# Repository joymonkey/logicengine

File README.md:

# logicengine
Info, Hardware Files and Arduino Sketches for the RSeries Logic Engine.

Assembly instructions and documentation can be found in the GitHub wiki here...
https://github.com/joymonkey/logicengine/wiki

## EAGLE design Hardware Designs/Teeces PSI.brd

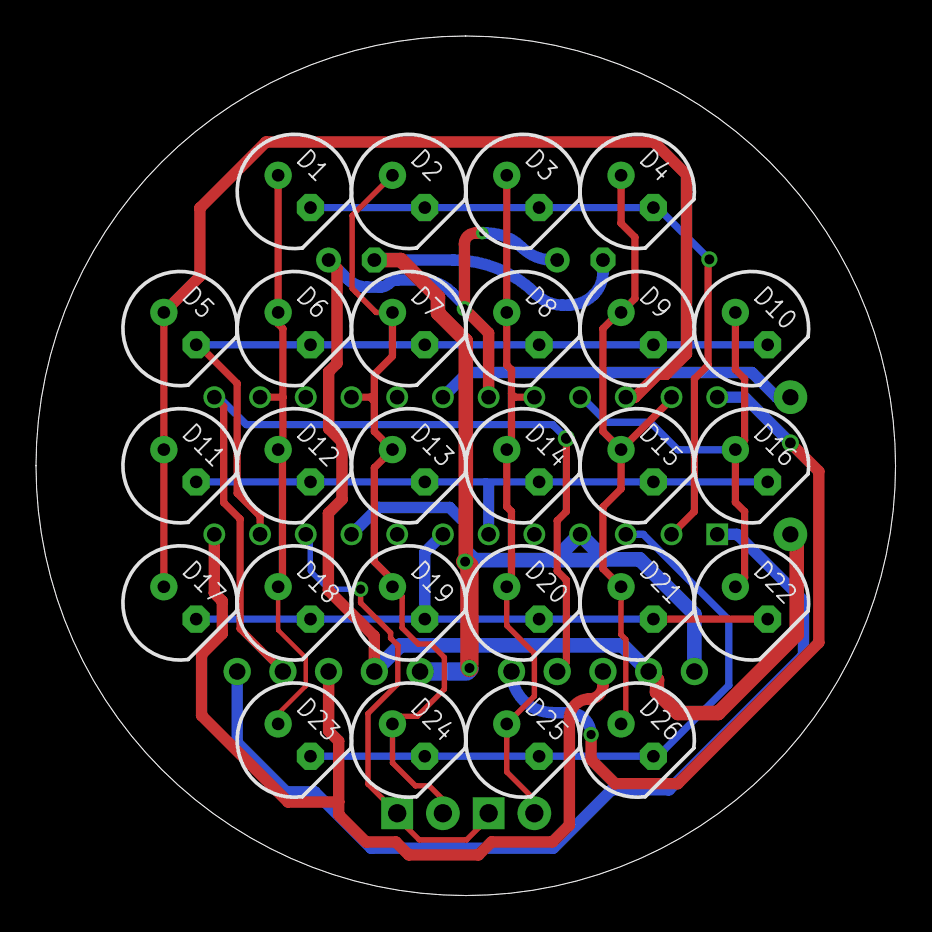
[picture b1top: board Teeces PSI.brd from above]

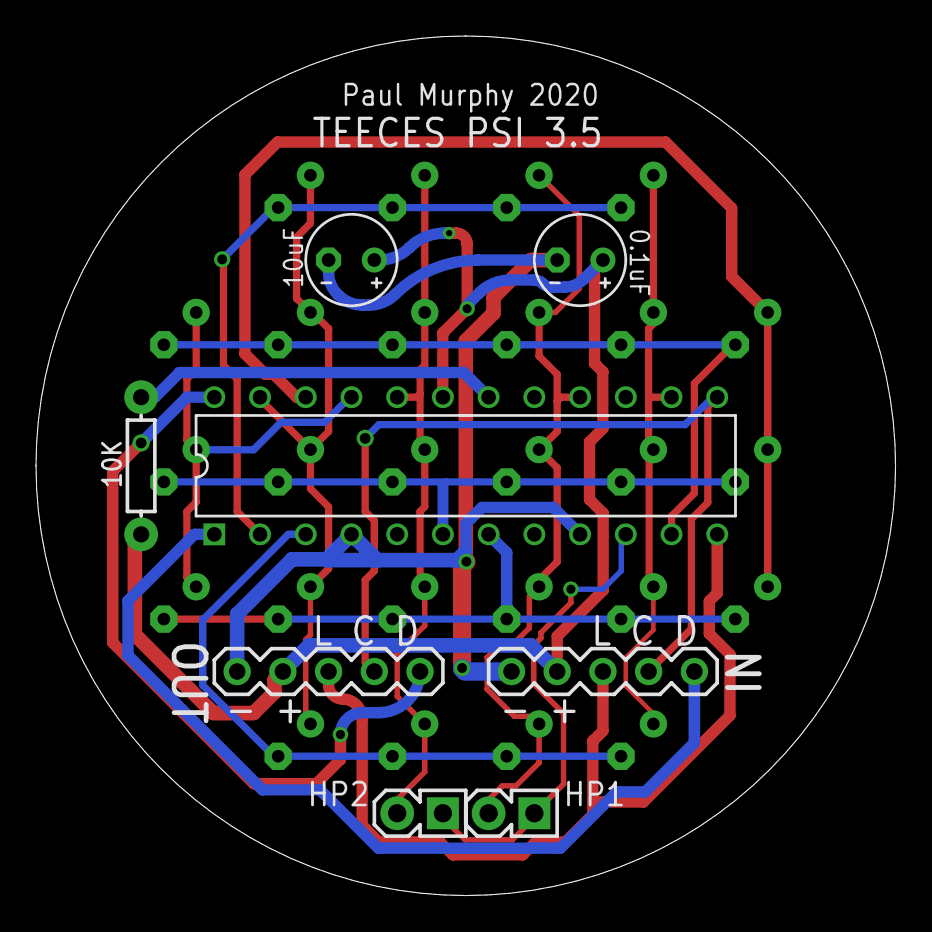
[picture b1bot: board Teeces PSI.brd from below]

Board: 2 copper layers, 47.8 x 47.8 mm, 34 parts (8 on the bottom side), 19 nets.

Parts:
C5: 10uF; E2,5-5
C6: 0.1uF; E2,5-5
D1, D2, D3, D4, D5, D6, D7, D8, D9, D10, D11, D12, D13, D14, D15, D16, D17, D18, D19, D20, D21, D22, D23, D24, D25, D26: LED5MM_SLIM
HP1, HP2: 1X02-SQ
IC2: MAX7219CNG; DIP24-3
IN: 1X05
OUT: 1X05
R2: 10K; AXIAL-0.3

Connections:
+5V: C5.+, C6.+, IC2.19, IN.2, OUT.2, R2.P$2
CLK: IC2.13, IN.4, OUT.4
DIG0: D1.K, D2.K, D3.K, D4.K, IC2.2
DIG1: D5.K, D6.K, D7.K, D8.K, D9.K, D10.K, IC2.11
DIG2: D11.K, D12.K, D13.K, D14.K, D15.K, D16.K, IC2.6
DIG3: D17.K, D18.K, D19.K, D20.K, D21.K, D22.K, IC2.7
DIG4: D23.K, D24.K, D25.K, D26.K, IC2.3
DIG5: HP1.1, HP2.1, IC2.10
DIN: IC2.1, IN.5
DOUT: IC2.24, OUT.5
GND: C5.-, C6.-, IC2.4, IC2.9, IN.1, OUT.1
LOAD: IC2.12, IN.3, OUT.3
unnamed: IC2.18, R2.P$1
SEGA: D1.A, D6.A, D12.A, D18.A, D23.A, IC2.14
SEGB: D2.A, D7.A, D13.A, D19.A, D24.A, HP1.2, IC2.16
SEGC: D3.A, D8.A, D14.A, D20.A, D25.A, HP2.2, IC2.20
SEGD: D4.A, D9.A, D15.A, D21.A, D26.A, IC2.23
SEGDP: D5.A, D11.A, D17.A, IC2.22
SEGE: D10.A, D16.A, D22.A, IC2.21

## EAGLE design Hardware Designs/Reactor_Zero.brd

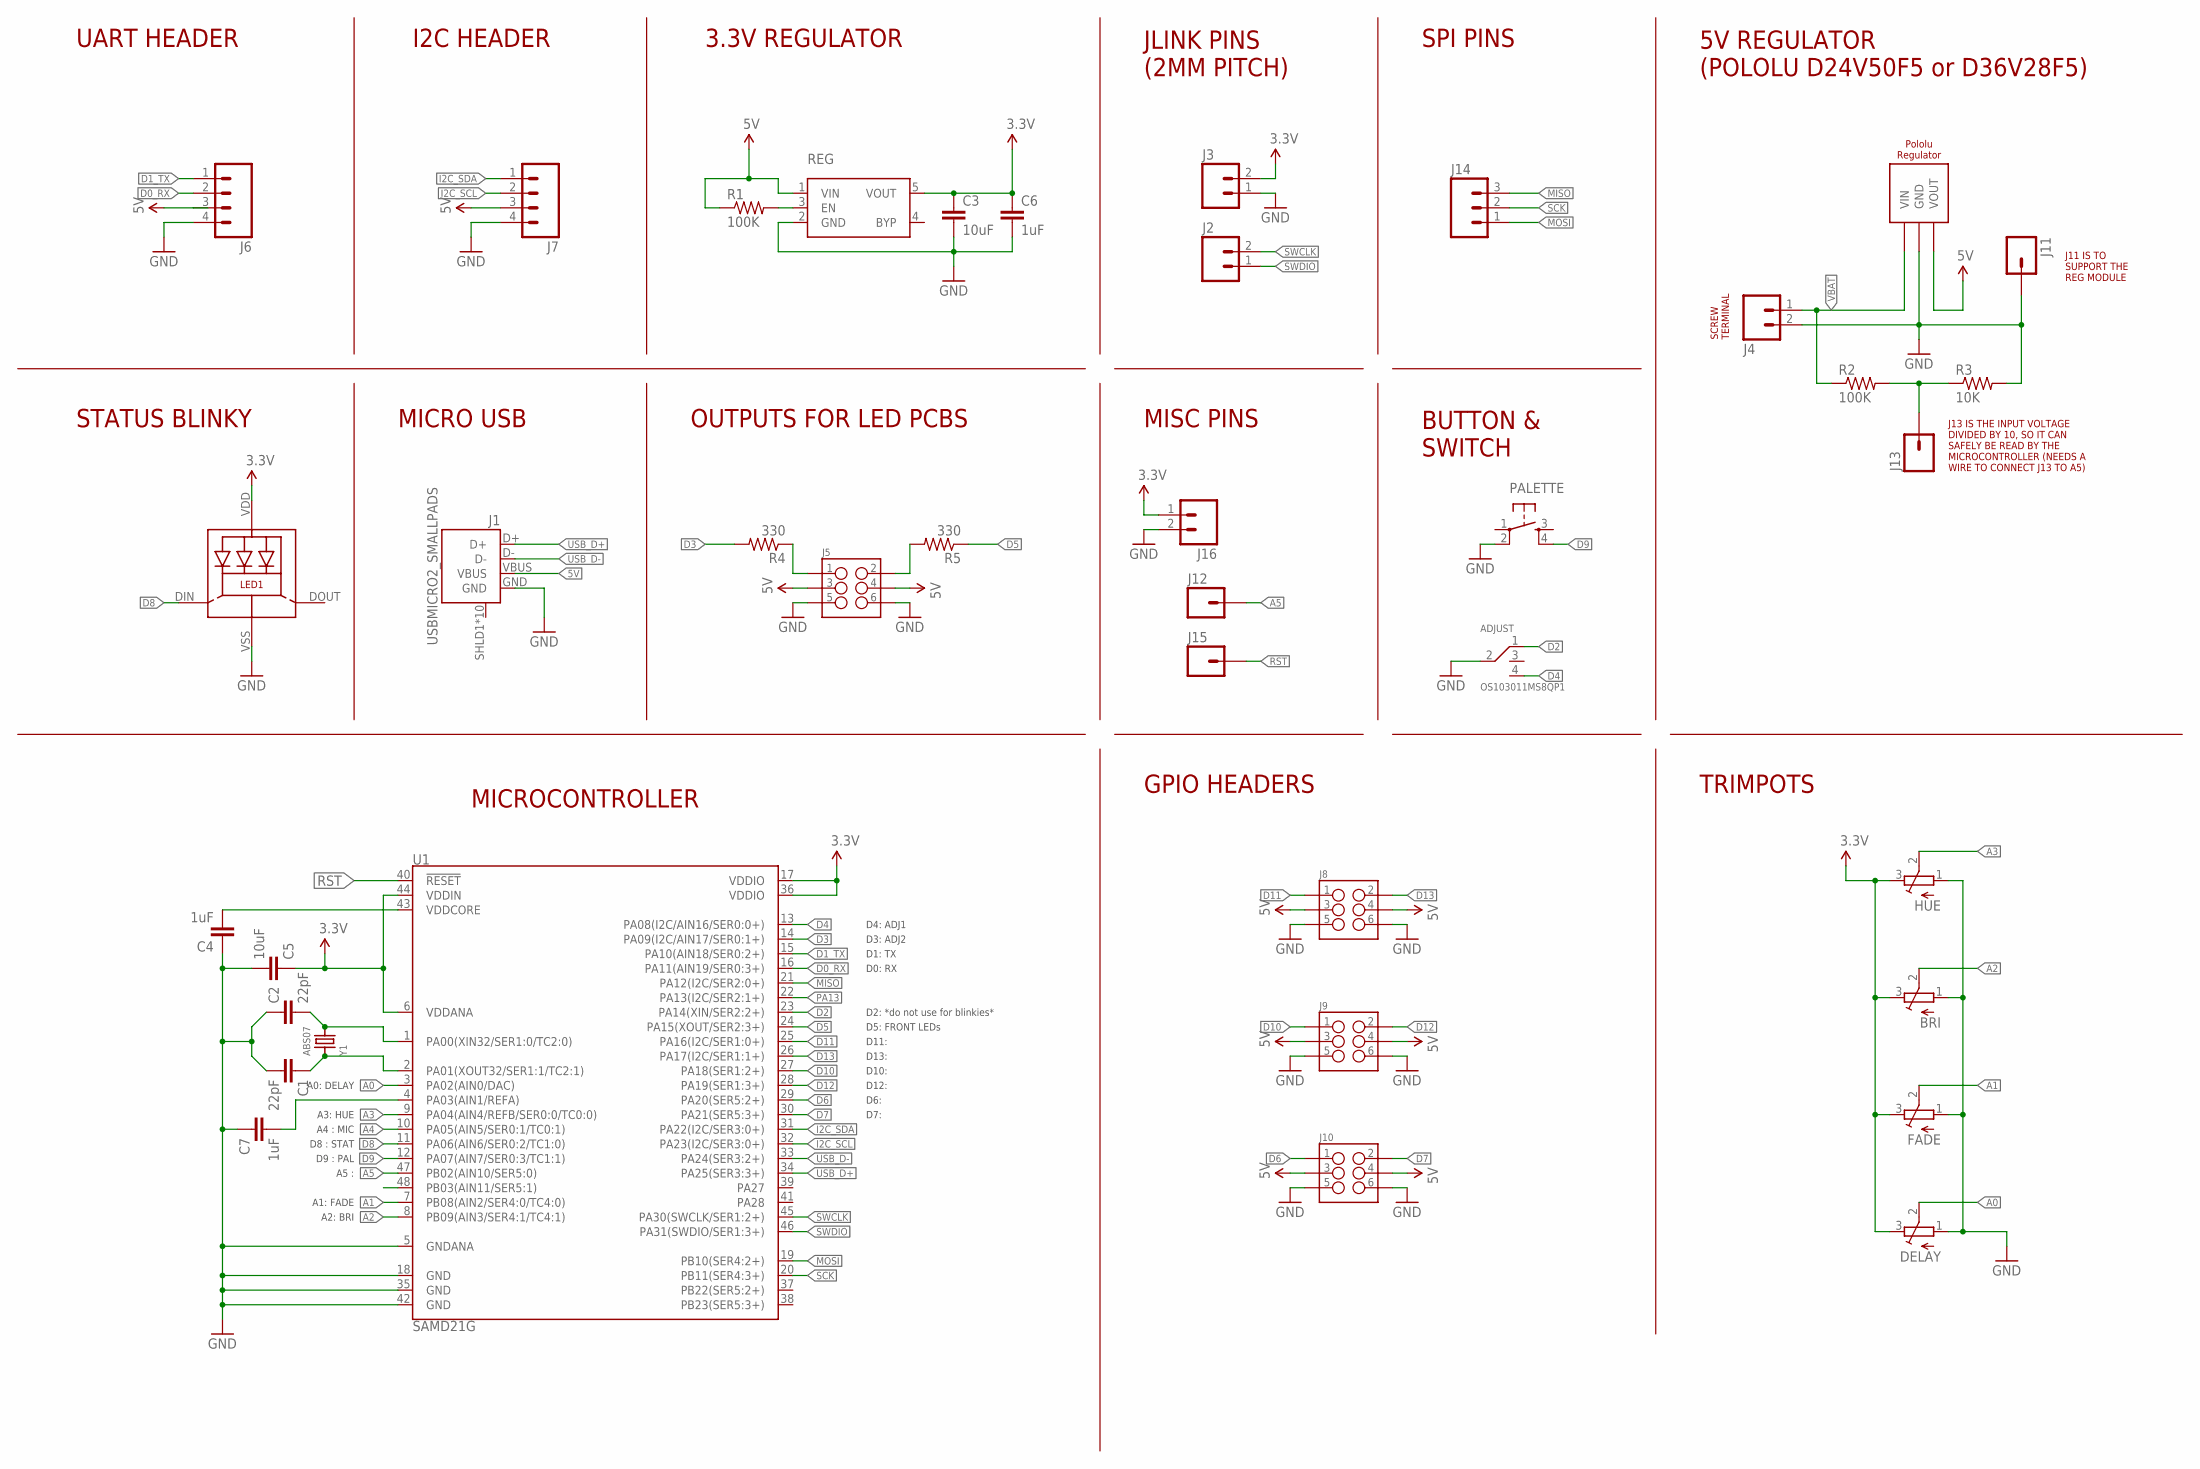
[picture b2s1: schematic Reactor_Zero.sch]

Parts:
ADJUST: OS103011MS8QP1
BRI: TRIMPOTEVM3V; EVM3V
C1, C2: 22pF; C0603K
C3, C5: 10uF; C0805K
C4, C6, C7: 1uF; C0805K
DELAY: TRIMPOTEVM3V; EVM3V
FADE: TRIMPOTEVM3V; EVM3V
HUE: TRIMPOTEVM3V; EVM3V
J1: USBMICRO2_SMALLPADS; USB-MICROB-10118194_SMALLPADS
J2, J3: M022MM; 1X02_NO_SILK_2MM
J4: M025MM; SCREWTERMINAL-5MM-2
J5, J8, J9, J10: M03X22X3_SILK_MALE_PTH; 2X3
J6, J7: M04PTH; 1X04
J11, J12, J13, J15: M01PTH; 1X01
J14: M03PTH; 1X03
J16: M02PTH; 1X02
LED1: WS2812BSK6812MINI-WIDE; SK6812MINI-WIDE
PALETTE: TAC_SWITCHPTH; TACTILE-PTH
R1, R2: 100K; R0603
R3: 10K; R0603
R4, R5: 330; R0603
REG: SPX3819; SOT23-5
U1: SAMD21G; TQFP-48_SMALL_PADS
U$1: POLOLU_REGD24V50FS_NO_HOLES; D24V50F5_NO_HOLES
Y1: ABS07

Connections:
3.3V: BRI.3 (E), C3.1, C5.1, C6.1, DELAY.3 (E), FADE.3 (E), HUE.3 (E), J3.2, J16.1, LED1.VDD, REG.5 (VOUT), U1.6 (VDDANA), U1.17 (VDDIO), U1.36 (VDDIO), U1.44 (VDDIN)
5V: J1.VBUS, J5.3, J5.4, J6.3, J7.3, J8.3, J8.4, J9.3, J9.4, J10.3, J10.4, R1.1, REG.1 (VIN), U$1.VOUT
A0: DELAY.2 (S), U1.3 (PA02(AIN0/DAC))
A1: FADE.2 (S), U1.7 (PB08(AIN2/SER4:0/TC4:0))
A2: BRI.2 (S), U1.8 (PB09(AIN3/SER4:1/TC4:1))
A3: HUE.2 (S), U1.9 (PA04(AIN4/REFB/SER0:0/TC0:0))
A4: U1.10 (PA05(AIN5/SER0:1/TC0:1))
A5: J12.1, U1.47 (PB02(AIN10/SER5:0))
AREF: C7.2, U1.4 (PA03(AIN1/REFA))
D0_RX: J6.2, U1.16 (PA11(AIN19/SER0:3+))
D1_TX: J6.1, U1.15 (PA10(AIN18/SER0:2+))
D2: ADJUST.1 (T1), U1.23 (PA14(XIN/SER2:2+))
D3: R4.2, U1.14 (PA09(I2C/AIN17/SER0:1+))
D4: ADJUST.4 (T3), U1.13 (PA08(I2C/AIN16/SER0:0+))
D5: R5.1, U1.24 (PA15(XOUT/SER2:3+))
D6: J10.1, U1.29 (PA20(SER5:2+))
D7: J10.2, U1.30 (PA21(SER5:3+))
D8: LED1.DIN (DI), U1.11 (PA06(AIN6/SER0:2/TC1:0))
D9: PALETTE.4, U1.12 (PA07(AIN7/SER0:3/TC1:1))
D10: J9.1, U1.27 (PA18(SER1:2+))
D11: J8.1, U1.25 (PA16(I2C/SER1:0+))
D12: J9.2, U1.28 (PA19(SER1:3+))
D13: J8.2, U1.26 (PA17(I2C/SER1:1+))
DIV: J13.1, R2.2, R3.1
GND: ADJUST.2, BRI.1 (A), C1.2, C2.1, C3.2, C4.1, C5.2, C6.2, C7.1, DELAY.1 (A), FADE.1 (A), HUE.1 (A), J1.GND, J3.1, J4.2, J5.5, J5.6, J6.4, J7.4, J8.5, J8.6, J9.5, J9.6, J10.5, J10.6, J11.1, J16.2, LED1.VSS (GND), PALETTE.2, R3.2, REG.2 (GND), U1.5 (GNDANA), U1.18 (GND), U1.35 (GND), U1.42 (GND), U$1.GND1 (GND), U$1.GND2 (GND)
I2C_SCL: J7.2, U1.32 (PA23(I2C/SER3:0+))
I2C_SDA: J7.1, U1.31 (PA22(I2C/SER3:0+))
MISO: J14.3, U1.21 (PA12(I2C/SER2:0+))
MOSI: J14.1, U1.19 (PB10(SER4:2+))
unnamed: C2.2, U1.1 (PA00(XIN32/SER1:0/TC2:0)), Y1.2
unnamed: C1.1, U1.2 (PA01(XOUT32/SER1:1/TC2:1)), Y1.1
unnamed: J5.2, R5.2
unnamed: R1.2, REG.3 (EN)
unnamed: J5.1, R4.1
unnamed: C4.2, U1.43 (VDDCORE)
PA13: U1.22 (PA13(I2C/SER2:1+))
RST: J15.1, U1.40 (!RESET!)
SCK: J14.2, U1.20 (PB11(SER4:3+))
SWCLK: J2.2, U1.45 (PA30(SWCLK/SER1:2+))
SWDIO: J2.1, U1.46 (PA31(SWDIO/SER1:3+))
USB_D+: J1.D+, U1.34 (PA25(SER3:3+))
USB_D-: J1.D-, U1.33 (PA24(SER3:2+))
VBAT: J4.1, R2.1, U$1.VIN

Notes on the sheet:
A0: DELAY A3: HUE A4 : MIC D8 : STAT D9 : PAL A5 : A1: FADE A2: BRI
D4: ADJ1 D3: ADJ2 D1: TX D0: RX D2: *do not use for blinkies* D5: FRONT LEDs D11: D13: D10: D12: D6: D7:
STATUS BLINKY
MICRO USB
OUTPUTS FOR LED PCBS
MICROCONTROLLER
UART HEADER
I2C HEADER
3.3V REGULATOR
JLINK PINS (2MM PITCH)
SPI PINS
5V REGULATOR (POLOLU D24V50F5 or D36V28F5)
J11 IS TO SUPPORT THE REG MODULE
J13 IS THE INPUT VOLTAGE DIVIDED BY 10, SO IT CAN SAFELY BE READ BY THE MICROCONTROLLER (NEEDS A WIRE TO CONNECT J13 TO A5)
SCREW TERMINAL
MISC PINS
BUTTON & SWITCH
GPIO HEADERS
TRIMPOTS

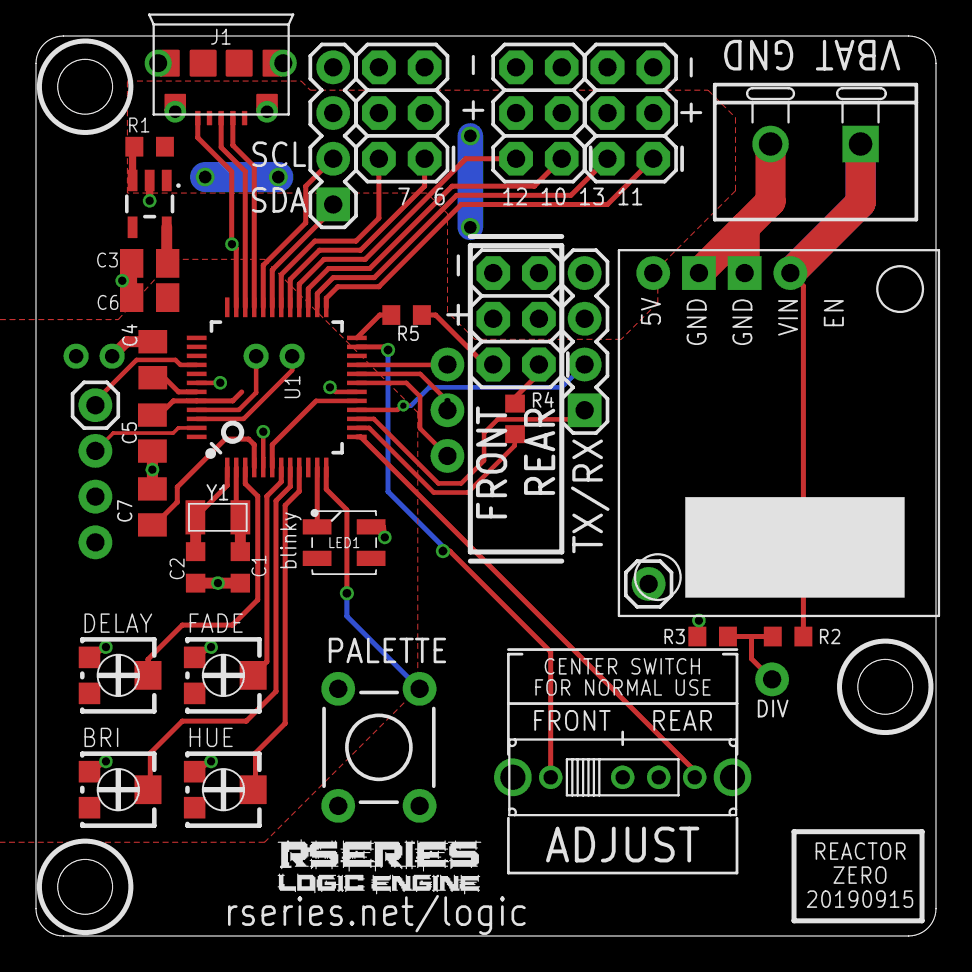
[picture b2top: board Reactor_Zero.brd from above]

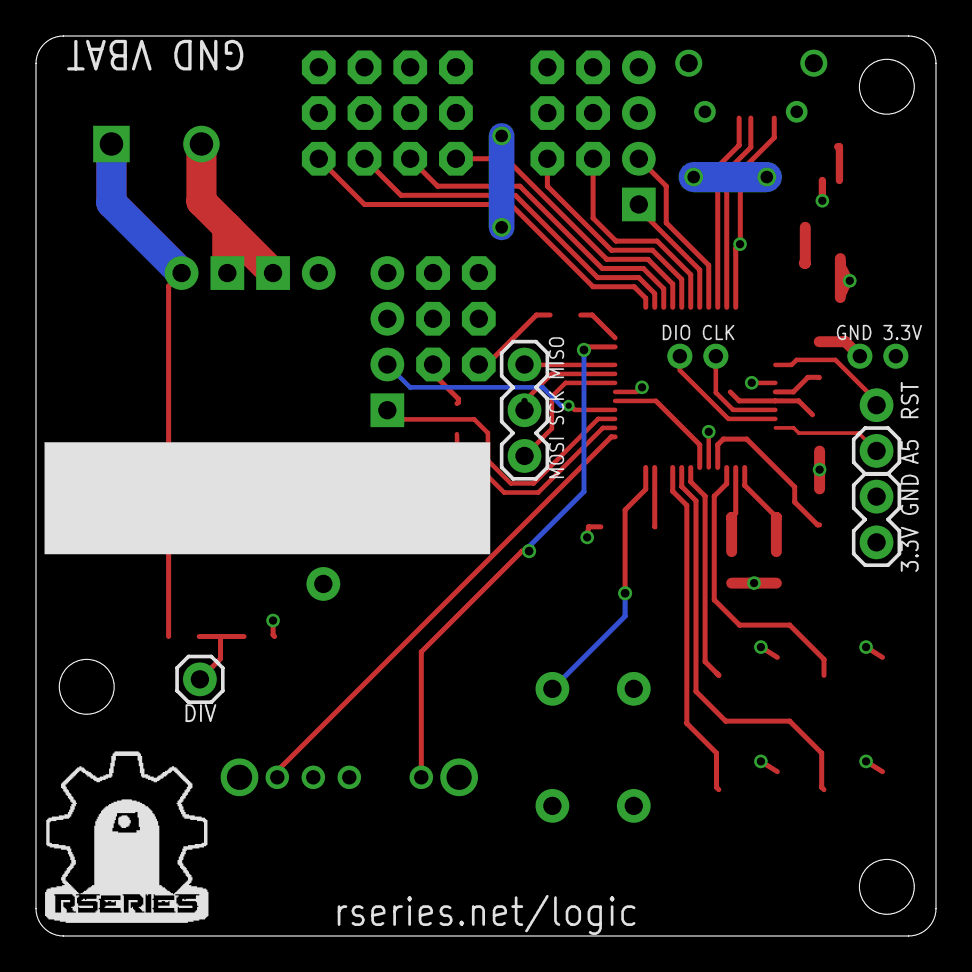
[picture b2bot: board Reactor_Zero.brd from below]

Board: 2 copper layers, 50.0 x 50.0 mm, 41 parts (5 on the bottom side), 41 nets.

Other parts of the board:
U$2: RSERIES_SMALL
U$4: RSERIES-LE-LOGO2

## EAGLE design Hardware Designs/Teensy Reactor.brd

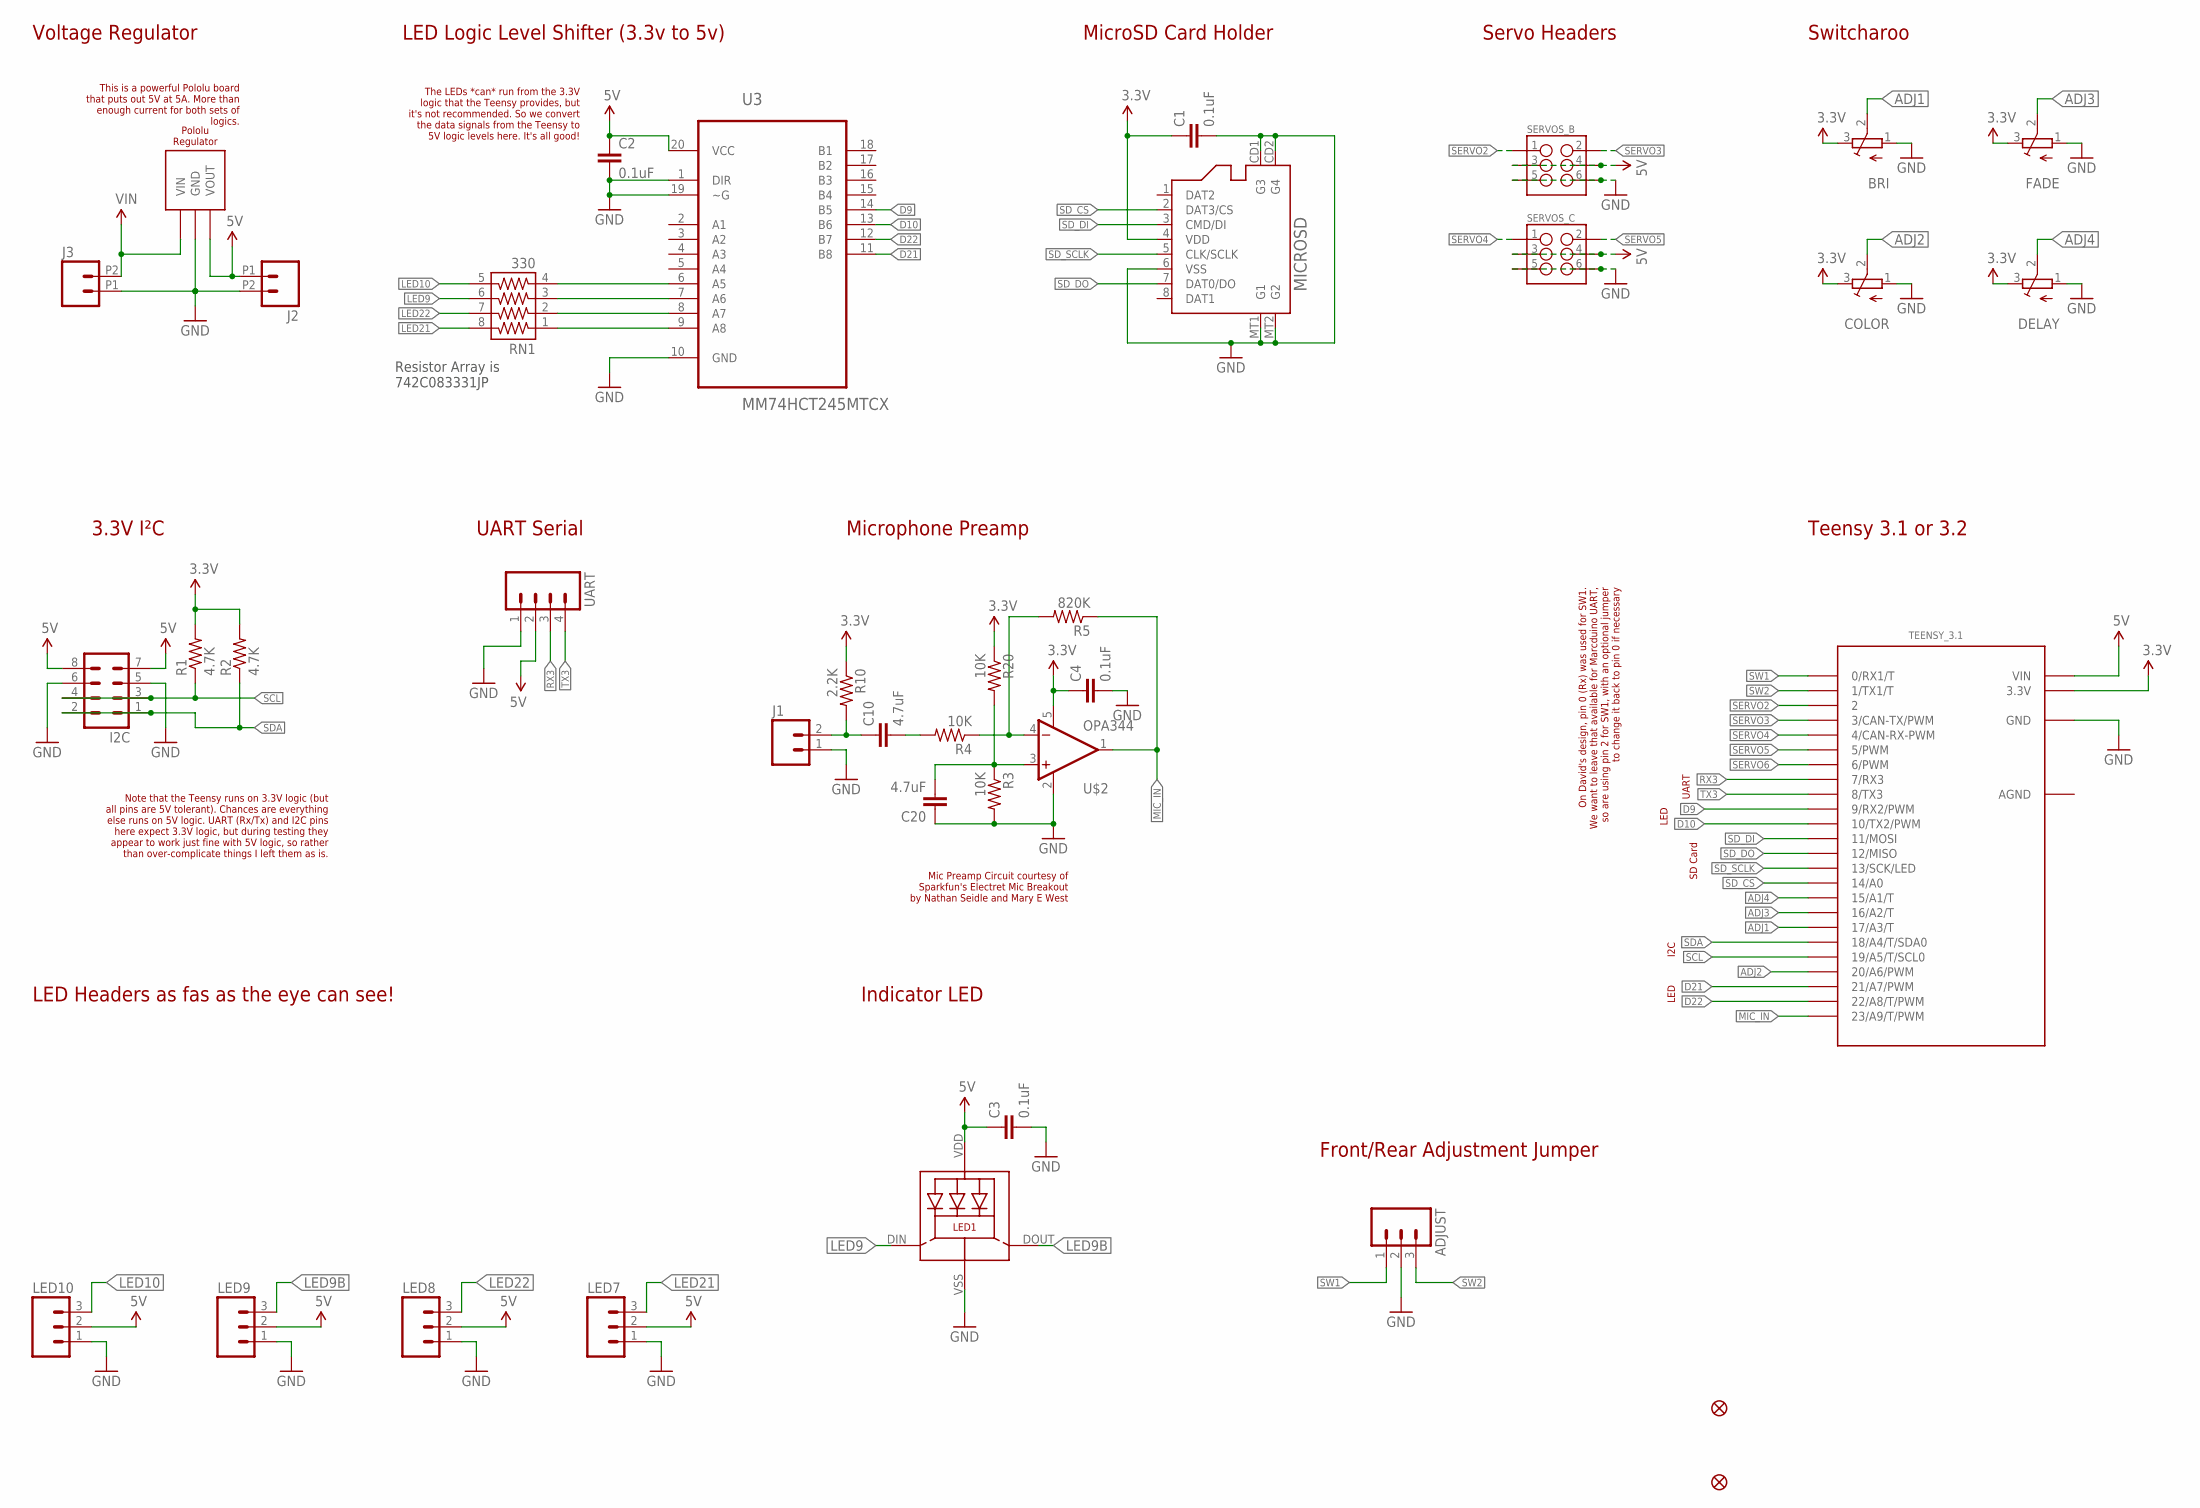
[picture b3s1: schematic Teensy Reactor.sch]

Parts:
ADJUST: M03PTH; 1X03
BRI: TRIMPOTEVM3V; EVM3V
C1, C2, C3, C4: 0.1uF; 0603-CAP
C10, C20: 4.7uF; 0603-CAP
COLOR: TRIMPOTEVM3V; EVM3V
DELAY: TRIMPOTEVM3V; EVM3V
FADE: TRIMPOTEVM3V; EVM3V
FID1, FID2: FIDUCIAL1X2; FIDUCIAL-1X2
I2C: M04X2; 2X4
J1: M02PTH; 1X02
J2, J3: M022.54MM_SCREWTERM; 1X02_2.54_SCREWTERM
LED1: WS2812BSK6812MINI; SK6812MINI
LED7, LED8, LED9, LED10: M03PTH; 1X03
MICROSD: MICROSD; MICROSD_SMALL
R1, R2: 4.7K; 0603-RES
R3, R4, R20: 10K; 0603-RES
R5: 820K; 0603-RES
R10: 2.2K; 0603-RES
RN1: 330; 742-8NS
SERVOS_B: M03X22X3_SILK_MALE_PTH; 2X3
SERVOS_C: M03X22X3_SILK_MALE_PTH; 2X3
TEENSY_3.1: TEENSY_3.1_SOME_PINS; TEENSY3-SOME_PINS
U3: MM74HCT245MTCX; SOP65P640X120-20N
U$1: POLOLU_REGD24V50FS_NO_HOLES; D24V50F5_NO_HOLES
U$2: OPA344; SOT23-5
UART: M04PTH; 1X04

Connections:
3.3V: BRI.3 (E), C1.1, C4.1, COLOR.3 (E), DELAY.3 (E), FADE.3 (E), MICROSD.4 (VDD), R1.2, R2.2, R10.1, R20.1, TEENSY_3.1.3.3V, TEENSY_3.1.3.3V1 (3.3V), U$2.5 (V+)
5V: C2.1, C3.1, I2C.7, I2C.8, J2.P1 (1), LED1.VDD, LED7.2, LED8.2, LED9.2, LED10.2, SERVOS_B.3, SERVOS_B.4, SERVOS_C.3, SERVOS_C.4, TEENSY_3.1.VIN, U3.20 (VCC), U$1.VOUT, UART.2
ADJ1: BRI.2 (S), TEENSY_3.1.17/A3 (17/A3/T)
ADJ2: COLOR.2 (S), TEENSY_3.1.20/A6 (20/A6/PWM)
ADJ3: FADE.2 (S), TEENSY_3.1.16/A2 (16/A2/T)
ADJ4: DELAY.2 (S), TEENSY_3.1.15/A1 (15/A1/T)
AGND: TEENSY_3.1.AGND
D9: TEENSY_3.1.9 (9/RX2/PWM), U3.14 (B5)
D10: TEENSY_3.1.10 (10/TX2/PWM), U3.13 (B6)
D21: TEENSY_3.1.21/A7 (21/A7/PWM), U3.11 (B8)
D22: TEENSY_3.1.22/A8 (22/A8/T/PWM), U3.12 (B7)
GND: ADJUST.2, BRI.1 (A), C1.2, C2.2, C3.2, C4.2, C20.1, COLOR.1 (A), DELAY.1 (A), FADE.1 (A), I2C.5, I2C.6, J1.1, J2.P2 (2), J3.P1 (1), LED1.VSS (GND), LED7.1, LED8.1, LED9.1, LED10.1, MICROSD.6 (VSS), MICROSD.CD1 (G3), MICROSD.CD2 (G4), MICROSD.MT1 (G1), MICROSD.MT2 (G2), R3.2, SERVOS_B.5, SERVOS_B.6, SERVOS_C.5, SERVOS_C.6, TEENSY_3.1.GND, TEENSY_3.1.GND1 (GND), U3.1 (DIR), U3.10 (GND), U3.19 (~G), U$1.GND1 (GND), U$1.GND2 (GND), U$2.2 (V-), UART.1
LED9: LED1.DIN (DI), RN1.6
LED9B: LED1.DOUT (DO), LED9.3
LED10: LED10.3, RN1.5
LED21: LED7.3, RN1.8
LED22: LED8.3, RN1.7
MIC_IN: R5.1, TEENSY_3.1.23/A9 (23/A9/T/PWM), U$2.1 (OUT)
unnamed: R4.1, R5.2, U$2.4 (-IN)
unnamed: C20.2, R3.1, R20.2, U$2.3 (+IN)
unnamed: C10.1, J1.2, R10.2
unnamed: RN1.1, U3.9 (A8)
unnamed: RN1.2, U3.8 (A7)
unnamed: RN1.3, U3.7 (A6)
unnamed: RN1.4, U3.6 (A5)
unnamed: C10.2, R4.2
RX3: TEENSY_3.1.7 (7/RX3), UART.3
SCL: I2C.3, I2C.4, R1.1, TEENSY_3.1.19/A5 (19/A5/T/SCL0)
SDA: I2C.1, I2C.2, R2.1, TEENSY_3.1.18/A4 (18/A4/T/SDA0)
SD_CS: MICROSD.2 (DAT3/CS), TEENSY_3.1.14/A0
SD_DI: MICROSD.3 (CMD/DI), TEENSY_3.1.11 (11/MOSI)
SD_DO: MICROSD.7 (DAT0/DO), TEENSY_3.1.12 (12/MISO)
SD_SCLK: MICROSD.5 (CLK/SCLK), TEENSY_3.1.13 (13/SCK/LED)
SERVO2: SERVOS_B.1, TEENSY_3.1.2
SERVO3: SERVOS_B.2, TEENSY_3.1.3 (3/CAN-TX/PWM)
SERVO4: SERVOS_C.1, TEENSY_3.1.4 (4/CAN-RX-PWM)
SERVO5: SERVOS_C.2, TEENSY_3.1.5 (5/PWM)
SERVO6: TEENSY_3.1.6 (6/PWM)
SW1: ADJUST.1, TEENSY_3.1.0 (0/RX1/T)
SW2: ADJUST.3, TEENSY_3.1.1 (1/TX1/T)
TX3: TEENSY_3.1.8 (8/TX3), UART.4
VIN: J3.P2 (2), U$1.VIN

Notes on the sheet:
Voltage Regulator
LED Headers as fas as the eye can see!
MicroSD Card Holder
LED Logic Level Shifter (3.3v to 5v)
3.3V I²C
Resistor Array is 742C083331JP
On David's design, pin 0 (Rx) was used for SW1. We want to leave that available for Marcduino UART, so are using pin 2 for SW1, with an optional jumper to change it back to pin 0 if necessary
Switcharoo
Note that the Teensy runs on 3.3V logic (but all pins are 5V tolerant). Chances are everything else runs on 5V logic. UART (Rx/Tx) and I2C pins here expect 3.3V logic, but during testing they appear to work just fine with 5V logic, so rather than over-complicate things I left them as is.
This is a powerful Pololu board that puts out 5V at 5A. More than enough current for both sets of logics.
The LEDs *can* run from the 3.3V logic that the Teensy provides, but it's not recommended. So we convert the data signals from the Teensy to 5V logic levels here. It's all good!
Servo Headers
Mic Preamp Circuit courtesy of Sparkfun's Electret Mic Breakout by Nathan Seidle and Mary E West
Microphone Preamp
UART Serial
Teensy 3.1 or 3.2
Indicator LED
Front/Rear Adjustment Jumper
LED
UART
I2C
SD Card

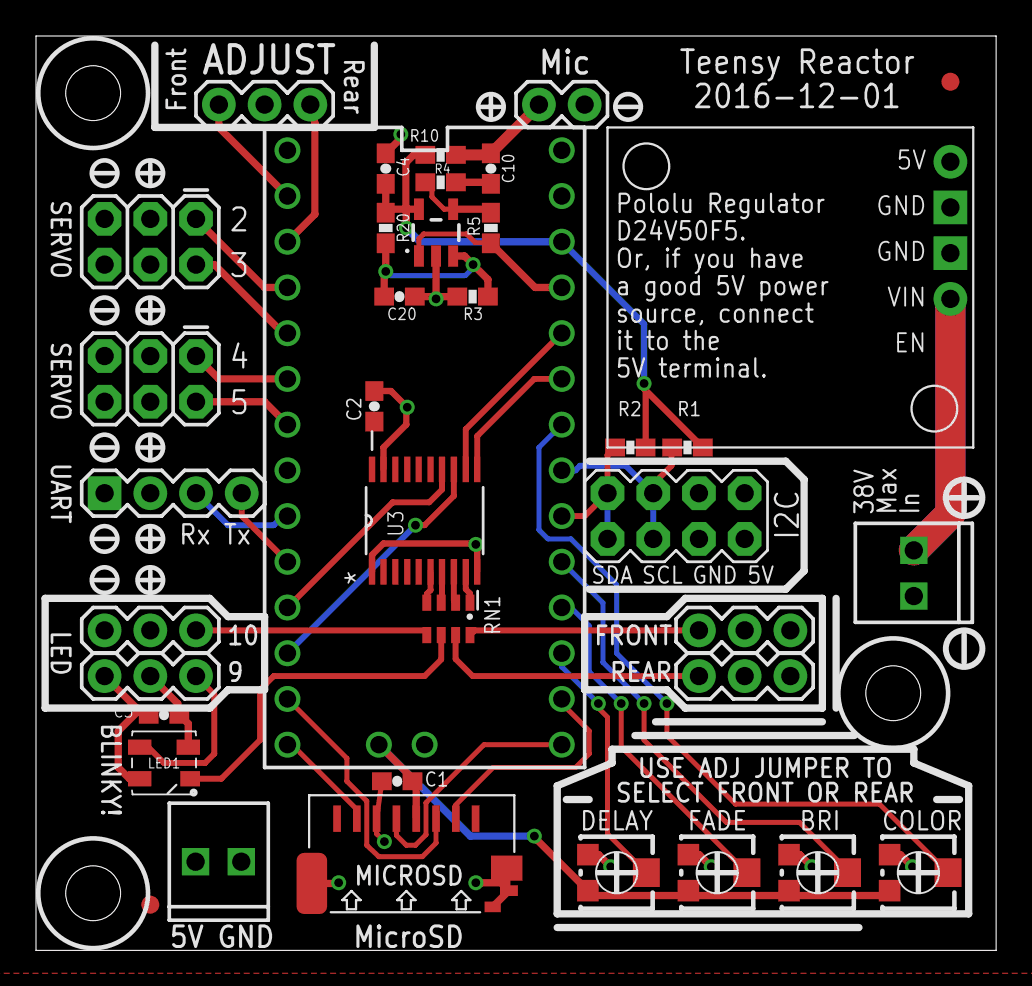
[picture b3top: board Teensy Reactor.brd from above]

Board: 2 copper layers, 53.3 x 50.8 mm, 38 parts (0 on the bottom side), 40 nets.

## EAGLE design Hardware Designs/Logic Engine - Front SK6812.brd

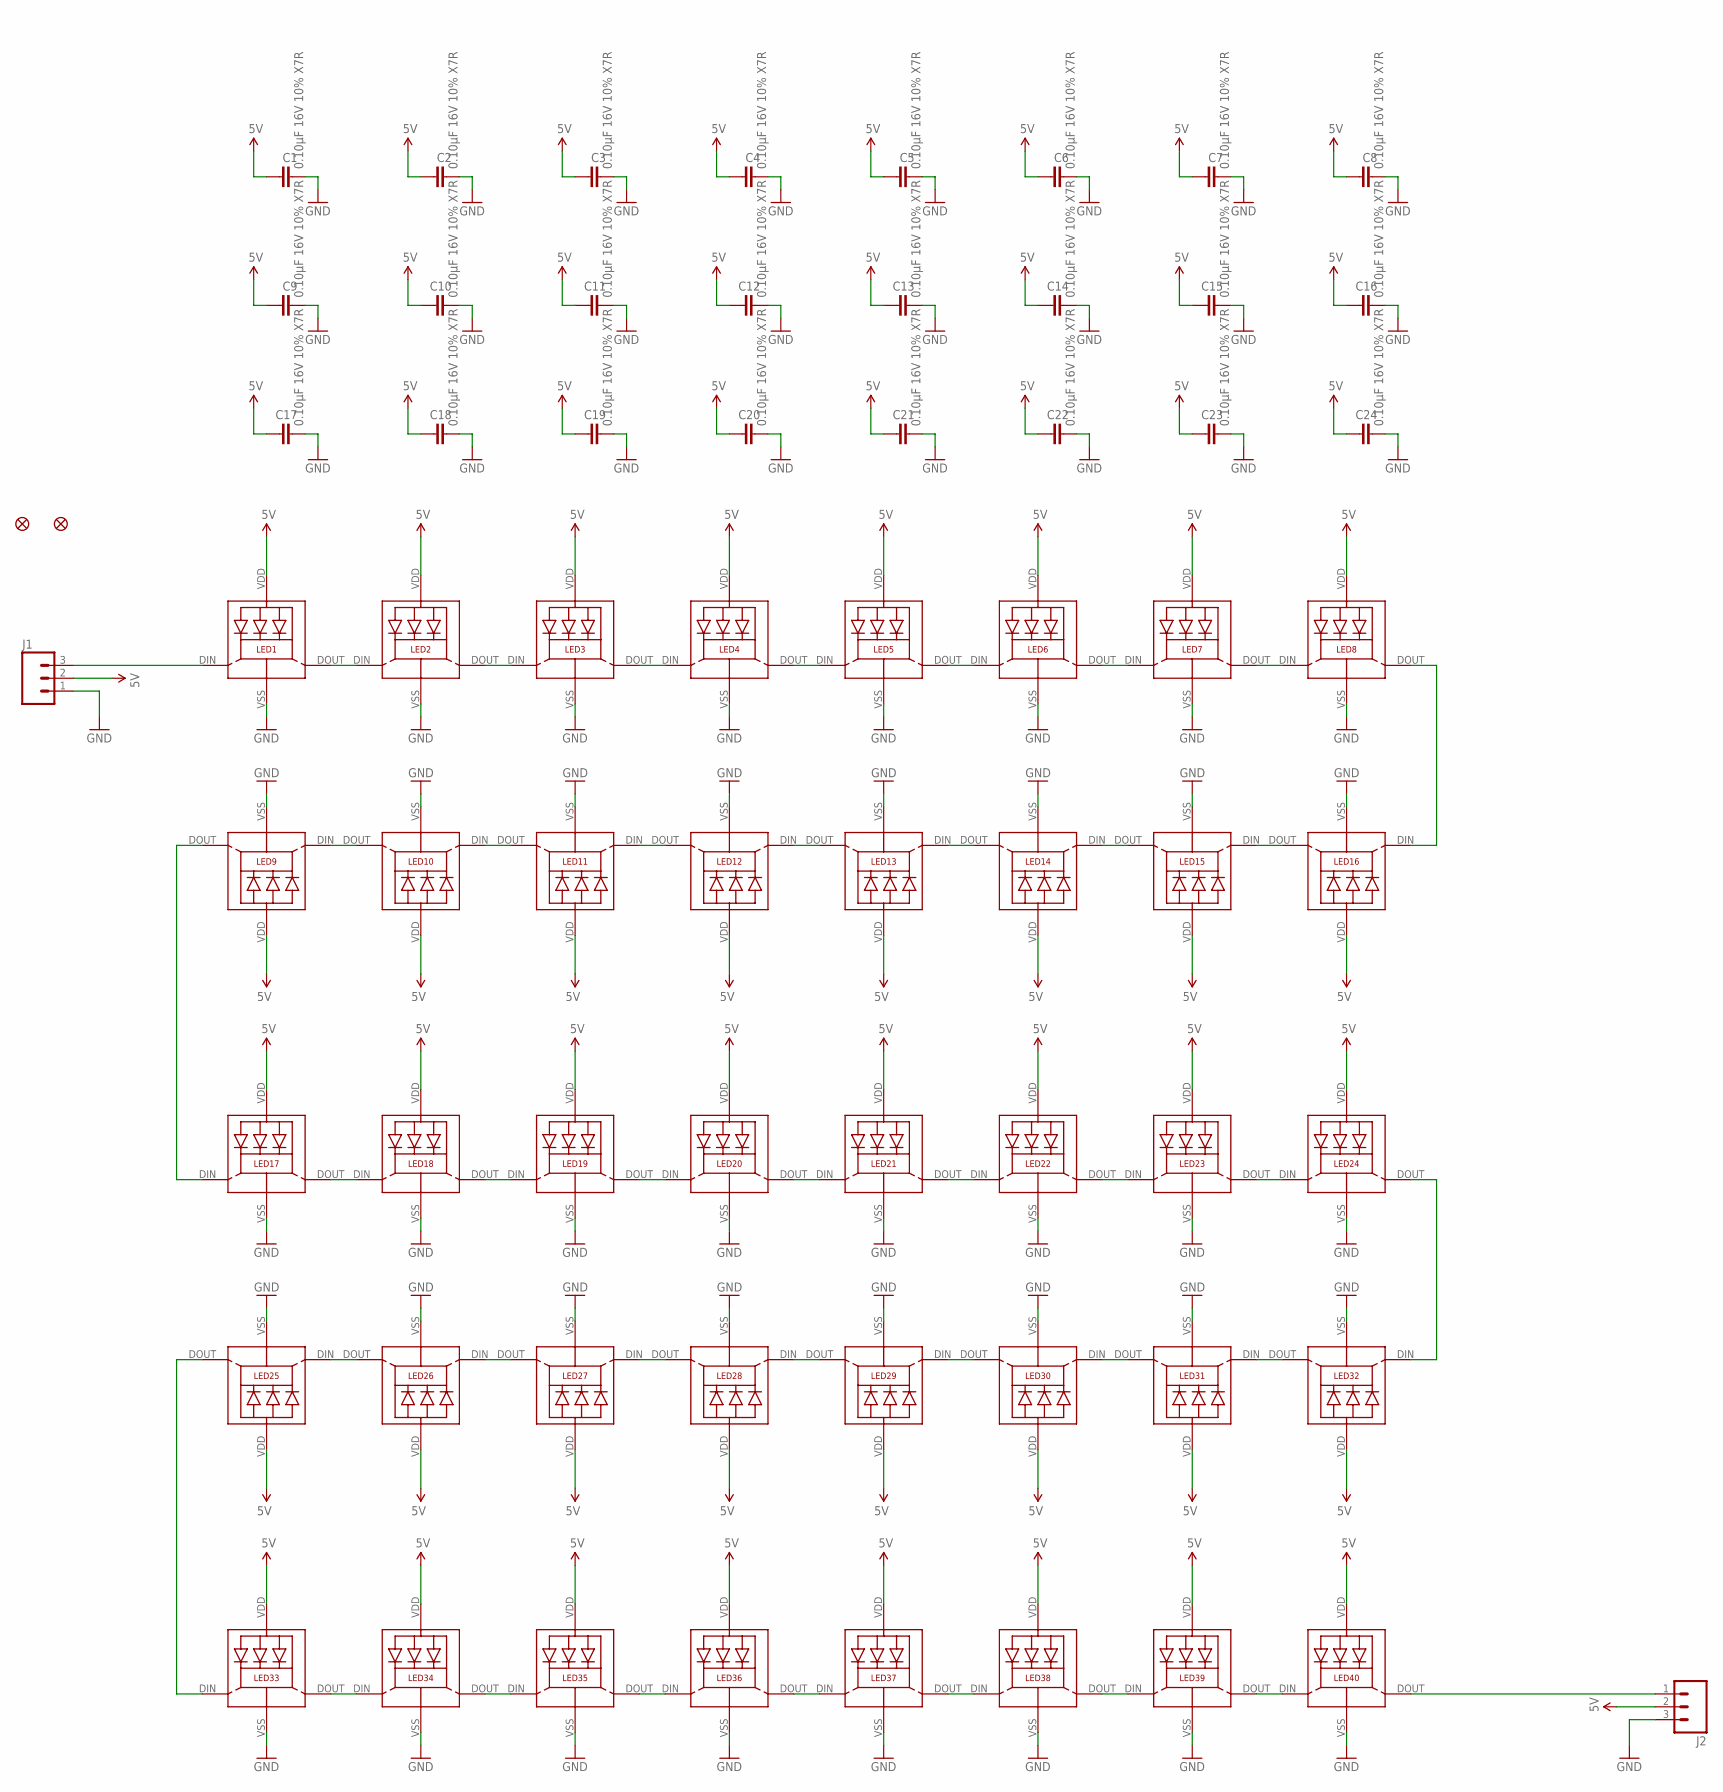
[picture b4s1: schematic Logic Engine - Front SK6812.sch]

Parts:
C1, C2, C3, C4, C5, C6, C7, C8, C9, C10, C11, C12, C13, C14, C15, C16, C17, C18, C19, C20, C21, C22, C23, C24: 0.10µF 16V 10% X7R; C0603
FD1, FD2: FIDUCIAL1X2; FIDUCIAL-1X2
J1, J2: M03PTH; 1X03
LED1, LED2, LED3, LED4, LED5, LED6, LED7, LED8, LED9, LED10, LED11, LED12, LED13, LED14, LED15, LED16, LED17, LED18, LED19, LED20, LED21, LED22, LED23, LED24, LED25, LED26, LED27, LED28, LED29, LED30, LED31, LED32, LED33, LED34, LED35, LED36, LED37, LED38, LED39, LED40: WS2812BSK6812MINI; SK6812MINI

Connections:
5V: C1.1, C2.1, C3.1, C4.1, C5.1, C6.1, C7.1, C8.1, C9.1, C10.1, C11.1, C12.1, C13.1, C14.1, C15.1, C16.1, C17.1, C18.1, C19.1, C20.1, C21.1, C22.1, C23.1, C24.1, J1.2, J2.2, LED1.VDD, LED2.VDD, LED3.VDD, LED4.VDD, LED5.VDD, LED6.VDD, LED7.VDD, LED8.VDD, LED9.VDD, LED10.VDD, LED11.VDD, LED12.VDD, LED13.VDD, LED14.VDD, LED15.VDD, LED16.VDD, LED17.VDD, LED18.VDD, LED19.VDD, LED20.VDD, LED21.VDD, LED22.VDD, LED23.VDD, LED24.VDD, LED25.VDD, LED26.VDD, LED27.VDD, LED28.VDD, LED29.VDD, LED30.VDD, LED31.VDD, LED32.VDD, LED33.VDD, LED34.VDD, LED35.VDD, LED36.VDD, LED37.VDD, LED38.VDD, LED39.VDD, LED40.VDD
GND: C1.2, C2.2, C3.2, C4.2, C5.2, C6.2, C7.2, C8.2, C9.2, C10.2, C11.2, C12.2, C13.2, C14.2, C15.2, C16.2, C17.2, C18.2, C19.2, C20.2, C21.2, C22.2, C23.2, C24.2, J1.1, J2.3, LED1.VSS (GND), LED2.VSS (GND), LED3.VSS (GND), LED4.VSS (GND), LED5.VSS (GND), LED6.VSS (GND), LED7.VSS (GND), LED8.VSS (GND), LED9.VSS (GND), LED10.VSS (GND), LED11.VSS (GND), LED12.VSS (GND), LED13.VSS (GND), LED14.VSS (GND), LED15.VSS (GND), LED16.VSS (GND), LED17.VSS (GND), LED18.VSS (GND), LED19.VSS (GND), LED20.VSS (GND), LED21.VSS (GND), LED22.VSS (GND), LED23.VSS (GND), LED24.VSS (GND), LED25.VSS (GND), LED26.VSS (GND), LED27.VSS (GND), LED28.VSS (GND), LED29.VSS (GND), LED30.VSS (GND), LED31.VSS (GND), LED32.VSS (GND), LED33.VSS (GND), LED34.VSS (GND), LED35.VSS (GND), LED36.VSS (GND), LED37.VSS (GND), LED38.VSS (GND), LED39.VSS (GND), LED40.VSS (GND)
unnamed: LED1.DOUT (DO), LED2.DIN (DI)
unnamed: LED2.DOUT (DO), LED3.DIN (DI)
unnamed: LED3.DOUT (DO), LED4.DIN (DI)
unnamed: LED4.DOUT (DO), LED5.DIN (DI)
unnamed: LED5.DOUT (DO), LED6.DIN (DI)
unnamed: LED6.DOUT (DO), LED7.DIN (DI)
unnamed: LED7.DOUT (DO), LED8.DIN (DI)
unnamed: LED8.DOUT (DO), LED16.DIN (DI)
unnamed: LED15.DIN (DI), LED16.DOUT (DO)
unnamed: LED14.DIN (DI), LED15.DOUT (DO)
unnamed: LED13.DIN (DI), LED14.DOUT (DO)
unnamed: LED12.DIN (DI), LED13.DOUT (DO)
unnamed: LED11.DIN (DI), LED12.DOUT (DO)
unnamed: LED10.DIN (DI), LED11.DOUT (DO)
unnamed: LED9.DIN (DI), LED10.DOUT (DO)
unnamed: LED17.DOUT (DO), LED18.DIN (DI)
unnamed: LED18.DOUT (DO), LED19.DIN (DI)
unnamed: LED19.DOUT (DO), LED20.DIN (DI)
unnamed: LED20.DOUT (DO), LED21.DIN (DI)
unnamed: LED21.DOUT (DO), LED22.DIN (DI)
unnamed: LED22.DOUT (DO), LED23.DIN (DI)
unnamed: LED23.DOUT (DO), LED24.DIN (DI)
unnamed: LED24.DOUT (DO), LED32.DIN (DI)
unnamed: J2.1, LED40.DOUT (DO)
unnamed: LED9.DOUT (DO), LED17.DIN (DI)
unnamed: LED31.DIN (DI), LED32.DOUT (DO)
unnamed: LED30.DIN (DI), LED31.DOUT (DO)
unnamed: LED29.DIN (DI), LED30.DOUT (DO)
unnamed: LED28.DIN (DI), LED29.DOUT (DO)
unnamed: LED27.DIN (DI), LED28.DOUT (DO)
unnamed: LED26.DIN (DI), LED27.DOUT (DO)
unnamed: LED25.DIN (DI), LED26.DOUT (DO)
unnamed: LED33.DOUT (DO), LED34.DIN (DI)
unnamed: LED34.DOUT (DO), LED35.DIN (DI)
unnamed: LED35.DOUT (DO), LED36.DIN (DI)
unnamed: LED36.DOUT (DO), LED37.DIN (DI)
unnamed: LED37.DOUT (DO), LED38.DIN (DI)
unnamed: LED38.DOUT (DO), LED39.DIN (DI)
unnamed: LED39.DOUT (DO), LED40.DIN (DI)
unnamed: LED25.DOUT (DO), LED33.DIN (DI)
unnamed: J1.3, LED1.DIN (DI)

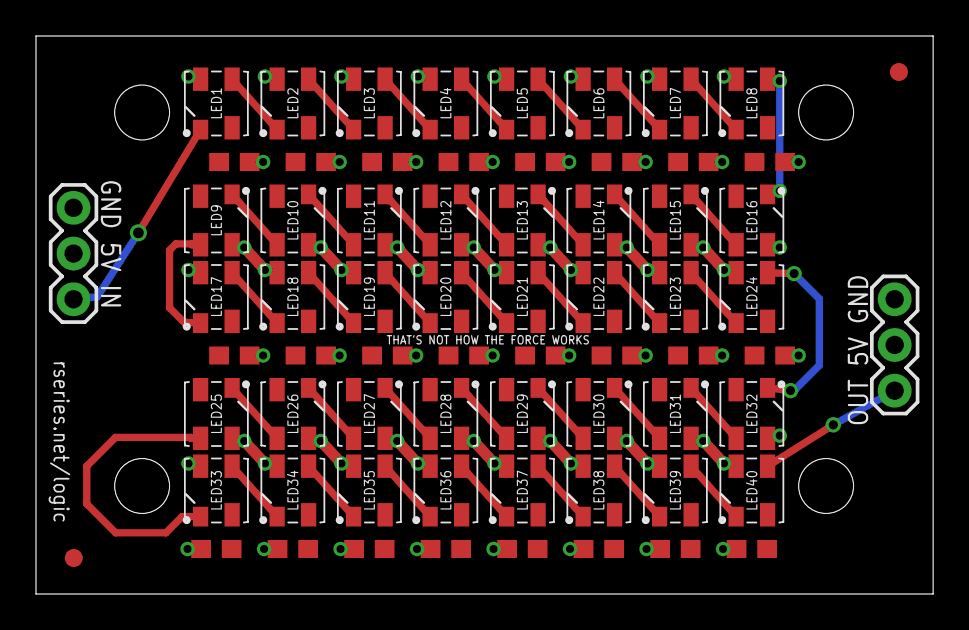
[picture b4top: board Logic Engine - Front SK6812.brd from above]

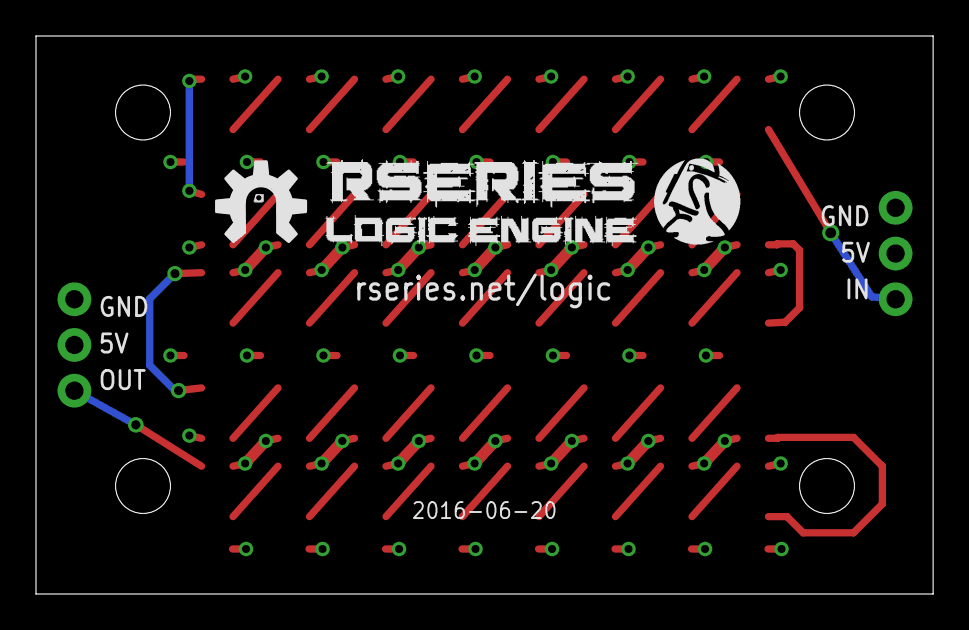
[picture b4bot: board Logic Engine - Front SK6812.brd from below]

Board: 2 copper layers, 49.8 x 31.0 mm, 71 parts (3 on the bottom side), 43 nets.

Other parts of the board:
U$1: RSERIES-LE-LOGO
U$2: R2BUILDERS-LOGO
U$3: RSERIES-OSHW-LOGO-MEDIUM

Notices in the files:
parts and their libraries:
SparkFun-DigitalIC: Licensing: CC v3.0 Share-Alike You are welcome to use this library for commercial purposes.
SparkFun-DiscreteSemi: Licensing: Creative Commons ShareAlike 4.0 International - https://creativecommons.org/licenses/by-sa/4.0
supply0: Copyright (C) 2007, Bob Starr
